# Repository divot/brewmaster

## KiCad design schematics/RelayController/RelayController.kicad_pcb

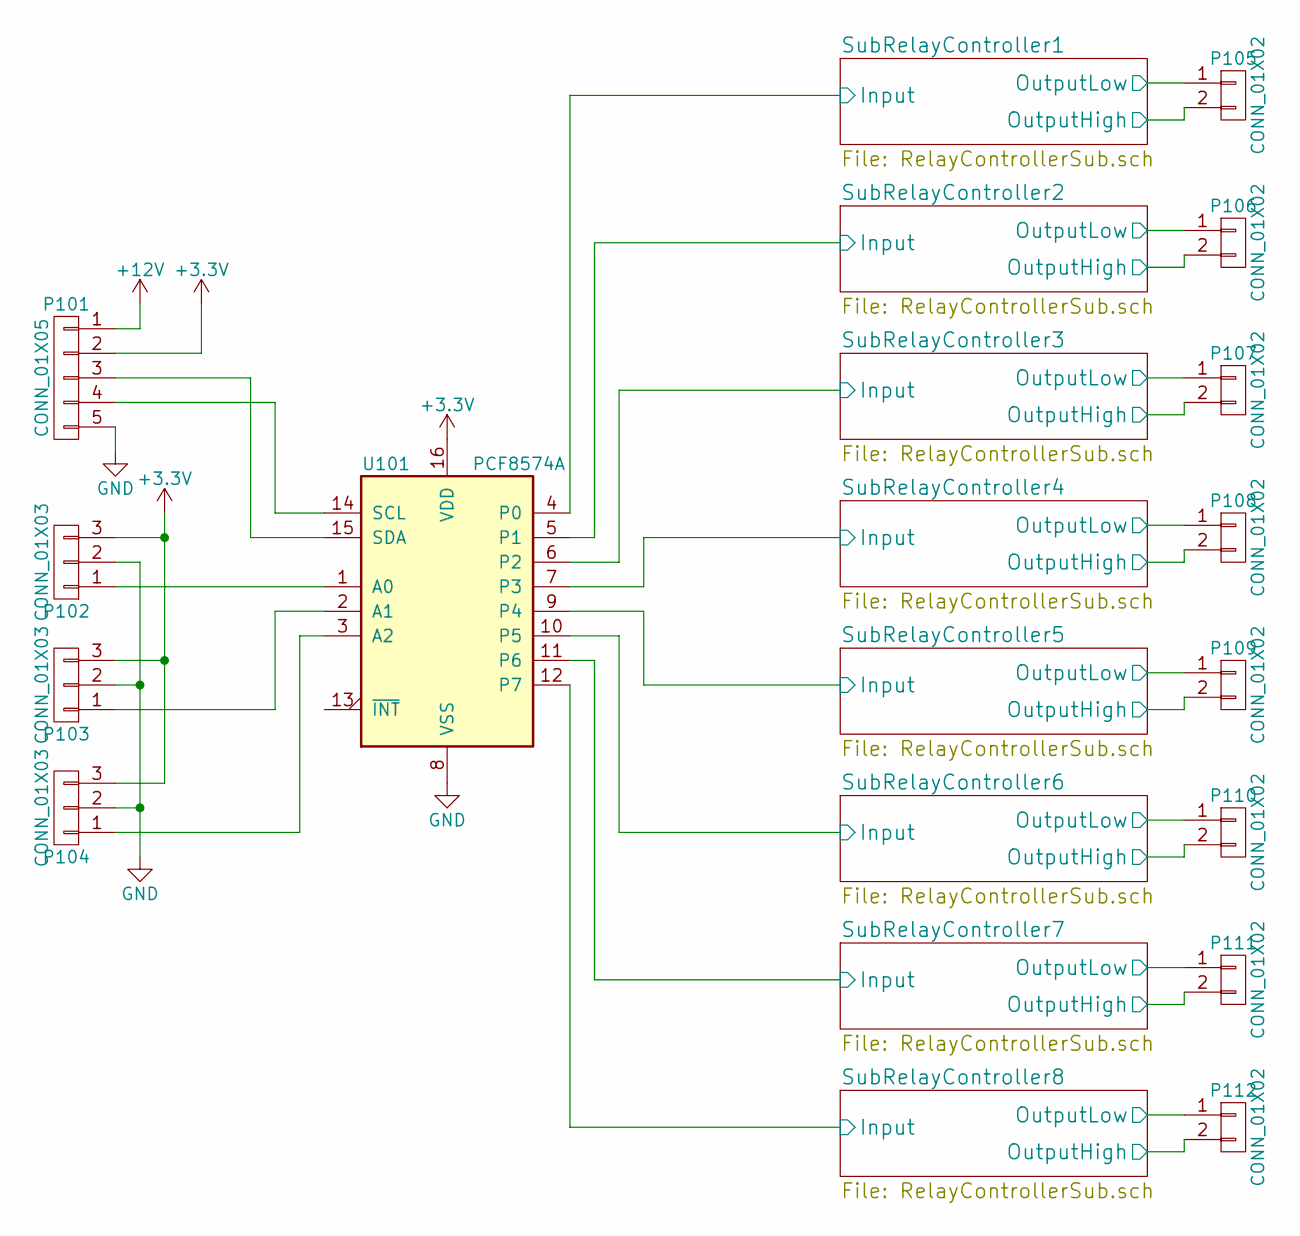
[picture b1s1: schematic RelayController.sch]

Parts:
P101: CONN_01X05; Pin_Header_Angled_1x05
P102, P103, P104: CONN_01X03; Pin_Header_Straight_1x03
P105, P106, P107, P108, P109, P110, P111, P112: CONN_01X02; Pin_Header_Angled_1x02
U101: PCF8574A; DIP-16_W7.62mm_LongPads

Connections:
+3V3: P101.2, P102.3, P103.3, P104.3, U101.16 (VDD); also elsewhere on the board
+12V: P101.1, P105.2, P106.2, P107.2, P108.2, P109.2, P110.2, P111.2, P112.2; also elsewhere on the board
/SubRelayController1/Input: U101.4 (P0); also elsewhere on the board
/SubRelayController1/OutputLow: P105.1; also elsewhere on the board
/SubRelayController2/Input: U101.5 (P1); also elsewhere on the board
/SubRelayController2/OutputLow: P106.1; also elsewhere on the board
/SubRelayController3/Input: U101.6 (P2); also elsewhere on the board
/SubRelayController3/OutputLow: P107.1; also elsewhere on the board
/SubRelayController4/Input: U101.7 (P3); also elsewhere on the board
/SubRelayController4/OutputLow: P108.1; also elsewhere on the board
/SubRelayController5/Input: U101.9 (P4); also elsewhere on the board
/SubRelayController5/OutputLow: P109.1; also elsewhere on the board
/SubRelayController6/Input: U101.10 (P5); also elsewhere on the board
/SubRelayController6/OutputLow: P110.1; also elsewhere on the board
/SubRelayController7/Input: U101.11 (P6); also elsewhere on the board
/SubRelayController7/OutputLow: P111.1; also elsewhere on the board
/SubRelayController8/Input: U101.12 (P7); also elsewhere on the board
/SubRelayController8/OutputLow: P112.1; also elsewhere on the board
GND: P101.5, P102.2, P103.2, P104.2, U101.8 (VSS); also elsewhere on the board
unnamed: P101.3, U101.15 (SDA)
unnamed: P101.4, U101.14 (SCL)
unnamed: P102.1, U101.1 (A0)
unnamed: P103.1, U101.2 (A1)
unnamed: P104.1, U101.3 (A2)

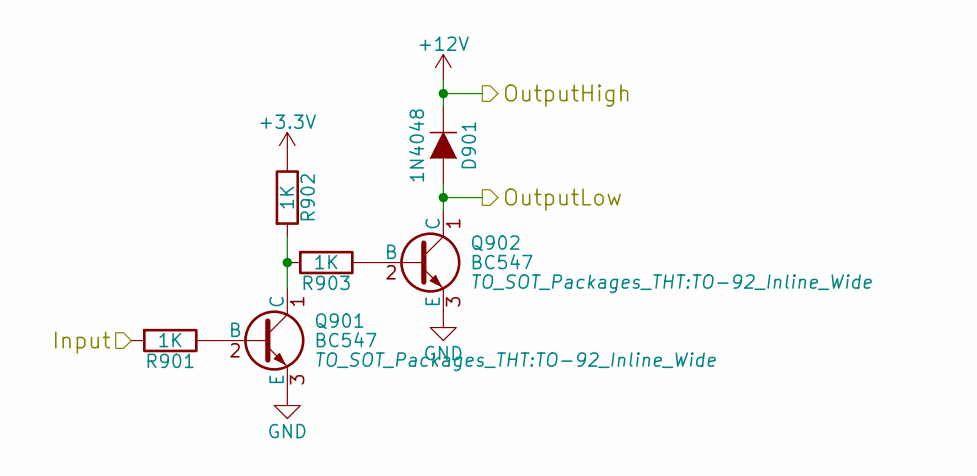
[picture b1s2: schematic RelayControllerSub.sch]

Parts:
D201: 1N4048; Diode_DO-35_SOD27_Horizontal_RM10
Q201, Q202: BC547; TO-92_Inline_Wide
R201, R202, R203: 1K; Resistor_Horizontal_RM10mm

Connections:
+3V3: R202.1; also elsewhere on the board
+12V: D201.1 (K); also elsewhere on the board
/SubRelayController1/Input: R201.2; also elsewhere on the board
/SubRelayController1/OutputLow: D201.2 (A), Q202.1 (C); also elsewhere on the board
GND: Q201.3 (E), Q202.3 (E); also elsewhere on the board
unnamed: Q201.1 (C), R202.2, R203.2
unnamed: Q201.2 (B), R201.1
unnamed: Q202.2 (B), R203.1

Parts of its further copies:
D301, D401, D501, D601, D701, D801, D901: 1N4048; Diode_DO-35_SOD27_Horizontal_RM10
Q301, Q302, Q401, Q402, Q501, Q502, Q601, Q602, Q701, Q702, Q801, Q802, Q901, Q902: BC547; TO-92_Inline_Wide
R301, R302, R303, R401, R402, R403, R501, R502, R503, R601, R602, R603, R701, R702, R703, R801, R802, R803, R901, R902, R903: 1K; Resistor_Horizontal_RM10mm

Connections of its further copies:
+3V3: R302.1, R402.1, R502.1, R602.1, R702.1, R802.1, R902.1; also elsewhere on the board
+12V: D301.1 (K), D401.1 (K), D501.1 (K), D601.1 (K), D701.1 (K), D801.1 (K), D901.1 (K); also elsewhere on the board
/SubRelayController2/Input: R301.2; also elsewhere on the board
/SubRelayController2/OutputLow: D301.2 (A), Q302.1 (C); also elsewhere on the board
/SubRelayController3/Input: R401.2; also elsewhere on the board
/SubRelayController3/OutputLow: D401.2 (A), Q402.1 (C); also elsewhere on the board
/SubRelayController4/Input: R501.2; also elsewhere on the board
/SubRelayController4/OutputLow: D501.2 (A), Q502.1 (C); also elsewhere on the board
/SubRelayController5/Input: R601.2; also elsewhere on the board
/SubRelayController5/OutputLow: D601.2 (A), Q602.1 (C); also elsewhere on the board
/SubRelayController6/Input: R701.2; also elsewhere on the board
/SubRelayController6/OutputLow: D701.2 (A), Q702.1 (C); also elsewhere on the board
/SubRelayController7/Input: R801.2; also elsewhere on the board
/SubRelayController7/OutputLow: D801.2 (A), Q802.1 (C); also elsewhere on the board
/SubRelayController8/Input: R901.2; also elsewhere on the board
/SubRelayController8/OutputLow: D901.2 (A), Q902.1 (C); also elsewhere on the board
GND: Q301.3 (E), Q302.3 (E), Q401.3 (E), Q402.3 (E), Q501.3 (E), Q502.3 (E), Q601.3 (E), Q602.3 (E), Q701.3 (E), Q702.3 (E), Q801.3 (E), Q802.3 (E), Q901.3 (E), Q902.3 (E); also elsewhere on the board
unnamed: Q301.1 (C), R302.2, R303.2
unnamed: Q301.2 (B), R301.1
unnamed: Q302.2 (B), R303.1
unnamed: Q401.1 (C), R402.2, R403.2
unnamed: Q401.2 (B), R401.1
unnamed: Q402.2 (B), R403.1
unnamed: Q501.1 (C), R502.2, R503.2
unnamed: Q501.2 (B), R501.1
unnamed: Q502.2 (B), R503.1
unnamed: Q601.1 (C), R602.2, R603.2
unnamed: Q601.2 (B), R601.1
unnamed: Q602.2 (B), R603.1
unnamed: Q701.1 (C), R702.2, R703.2
unnamed: Q701.2 (B), R701.1
unnamed: Q702.2 (B), R703.1
unnamed: Q801.1 (C), R802.2, R803.2
unnamed: Q801.2 (B), R801.1
unnamed: Q802.2 (B), R803.1
unnamed: Q901.1 (C), R902.2, R903.2
unnamed: Q901.2 (B), R901.1
unnamed: Q902.2 (B), R903.1

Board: 2 copper layers, 61 parts (0 on the bottom side), 48 nets, no tracks yet.

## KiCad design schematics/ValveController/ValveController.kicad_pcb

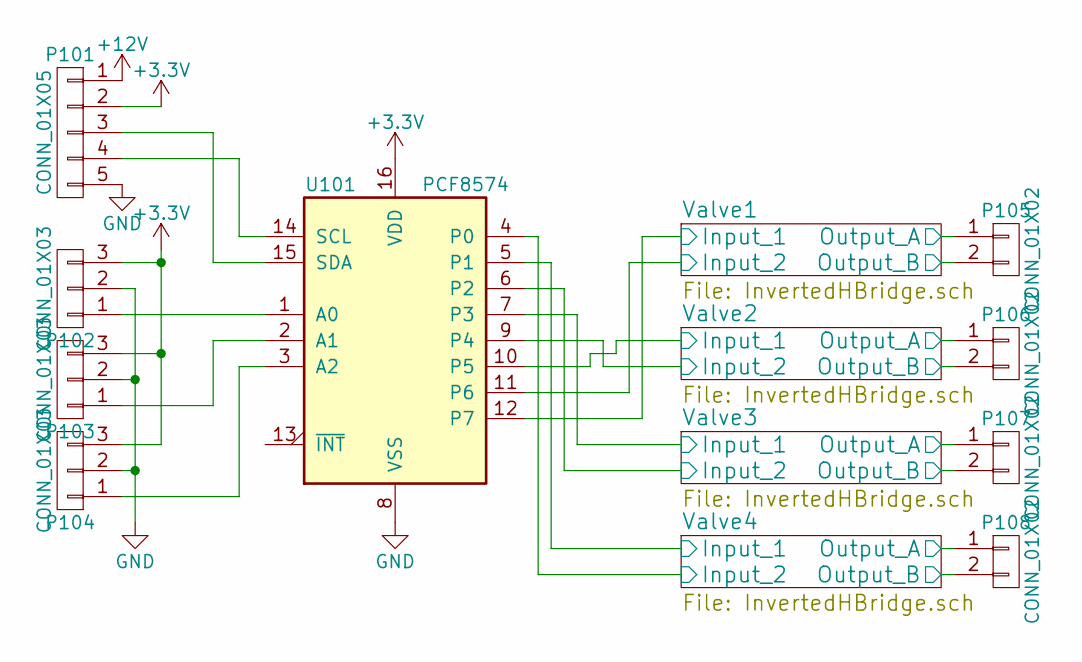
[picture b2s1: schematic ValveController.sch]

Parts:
P101: CONN_01X05; Pin_Header_Angled_1x05
P102, P103, P104: CONN_01X03; Pin_Header_Straight_1x03
P105, P106, P107, P108: CONN_01X02; Pin_Header_Angled_1x02
U101: PCF8574; DIP-16_W7.62mm_LongPads

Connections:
+3V3: P101.2, P102.3, P103.3, P104.3, U101.16 (VDD); also elsewhere on the board
+12V: P101.1; also elsewhere on the board
/Valve1/Input_1: U101.12 (P7); also elsewhere on the board
/Valve1/Input_2: U101.11 (P6); also elsewhere on the board
/Valve1/Output_A: P105.1; also elsewhere on the board
/Valve1/Output_B: P105.2; also elsewhere on the board
/Valve2/Input_1: U101.10 (P5); also elsewhere on the board
/Valve2/Input_2: U101.9 (P4); also elsewhere on the board
/Valve2/Output_A: P106.1; also elsewhere on the board
/Valve2/Output_B: P106.2; also elsewhere on the board
/Valve3/Input_1: U101.7 (P3); also elsewhere on the board
/Valve3/Input_2: U101.6 (P2); also elsewhere on the board
/Valve3/Output_A: P107.1; also elsewhere on the board
/Valve3/Output_B: P107.2; also elsewhere on the board
/Valve4/Input_1: U101.5 (P1); also elsewhere on the board
/Valve4/Input_2: U101.4 (P0); also elsewhere on the board
/Valve4/Output_A: P108.1; also elsewhere on the board
/Valve4/Output_B: P108.2; also elsewhere on the board
GND: P101.5, P102.2, P103.2, P104.2, U101.8 (VSS); also elsewhere on the board
unnamed: P101.3, U101.15 (SDA)
unnamed: P101.4, U101.14 (SCL)
unnamed: P102.1, U101.1 (A0)
unnamed: P103.1, U101.2 (A1)
unnamed: P104.1, U101.3 (A2)

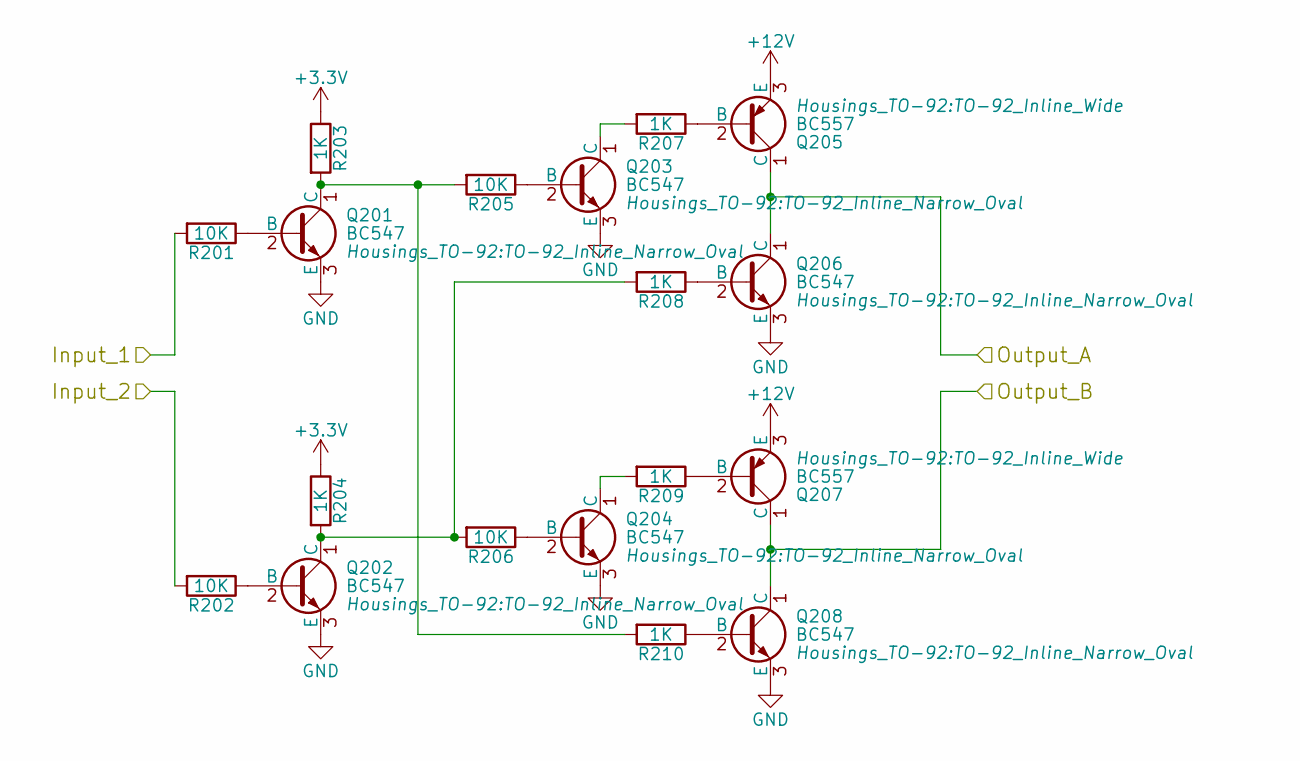
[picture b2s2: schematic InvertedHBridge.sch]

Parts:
Q201, Q202, Q203, Q204, Q206, Q208: BC547; TO-92_Inline_Narrow_Oval
Q205, Q207: BC557; TO-92_Inline_Wide
R201, R202, R205, R206: 10K; Resistor_Horizontal_RM10mm
R203, R204, R207, R208, R209, R210: 1K; Resistor_Horizontal_RM10mm

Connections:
+3V3: R203.1, R204.1; also elsewhere on the board
+12V: Q205.3 (E), Q207.3 (E); also elsewhere on the board
/Valve1/Input_1: R201.2; also elsewhere on the board
/Valve1/Input_2: R202.2; also elsewhere on the board
/Valve1/Output_A: Q205.1 (C), Q206.1 (C); also elsewhere on the board
/Valve1/Output_B: Q207.1 (C), Q208.1 (C); also elsewhere on the board
GND: Q201.3 (E), Q202.3 (E), Q203.3 (E), Q204.3 (E), Q206.3 (E), Q208.3 (E); also elsewhere on the board
unnamed: Q201.1 (C), R203.2, R205.2, R210.2
unnamed: Q201.2 (B), R201.1
unnamed: Q202.1 (C), R204.2, R206.2, R208.2
unnamed: Q202.2 (B), R202.1
unnamed: Q203.1 (C), R207.2
unnamed: Q203.2 (B), R205.1
unnamed: Q204.1 (C), R209.2
unnamed: Q204.2 (B), R206.1
unnamed: Q205.2 (B), R207.1
unnamed: Q206.2 (B), R208.1
unnamed: Q207.2 (B), R209.1
unnamed: Q208.2 (B), R210.1

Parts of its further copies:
Q301, Q302, Q303, Q304, Q306, Q308, Q401, Q402, Q403, Q404, Q406, Q408, Q501, Q502, Q503, Q504, Q506, Q508: BC547; TO-92_Inline_Narrow_Oval
Q305, Q307, Q405, Q407, Q505, Q507: BC557; TO-92_Inline_Wide
R301, R302, R305, R306, R401, R402, R405, R406, R501, R502, R505, R506: 10K; Resistor_Horizontal_RM10mm
R303, R304, R307, R308, R309, R310, R403, R404, R407, R408, R409, R410, R503, R504, R507, R508, R509, R510: 1K; Resistor_Horizontal_RM10mm

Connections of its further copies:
+3V3: R303.1, R304.1, R403.1, R404.1, R503.1, R504.1; also elsewhere on the board
+12V: Q305.3 (E), Q307.3 (E), Q405.3 (E), Q407.3 (E), Q505.3 (E), Q507.3 (E); also elsewhere on the board
/Valve2/Input_1: R301.2; also elsewhere on the board
/Valve2/Input_2: R302.2; also elsewhere on the board
/Valve2/Output_A: Q305.1 (C), Q306.1 (C); also elsewhere on the board
/Valve2/Output_B: Q307.1 (C), Q308.1 (C); also elsewhere on the board
/Valve3/Input_1: R401.2; also elsewhere on the board
/Valve3/Input_2: R402.2; also elsewhere on the board
/Valve3/Output_A: Q405.1 (C), Q406.1 (C); also elsewhere on the board
/Valve3/Output_B: Q407.1 (C), Q408.1 (C); also elsewhere on the board
/Valve4/Input_1: R501.2; also elsewhere on the board
/Valve4/Input_2: R502.2; also elsewhere on the board
/Valve4/Output_A: Q505.1 (C), Q506.1 (C); also elsewhere on the board
/Valve4/Output_B: Q507.1 (C), Q508.1 (C); also elsewhere on the board
GND: Q301.3 (E), Q302.3 (E), Q303.3 (E), Q304.3 (E), Q306.3 (E), Q308.3 (E), Q401.3 (E), Q402.3 (E), Q403.3 (E), Q404.3 (E), Q406.3 (E), Q408.3 (E), Q501.3 (E), Q502.3 (E), Q503.3 (E), Q504.3 (E), Q506.3 (E), Q508.3 (E); also elsewhere on the board
unnamed: Q301.1 (C), R303.2, R305.2, R310.2
unnamed: Q301.2 (B), R301.1
unnamed: Q302.1 (C), R304.2, R306.2, R308.2
unnamed: Q302.2 (B), R302.1
unnamed: Q303.1 (C), R307.2
unnamed: Q303.2 (B), R305.1
unnamed: Q304.1 (C), R309.2
unnamed: Q304.2 (B), R306.1
unnamed: Q305.2 (B), R307.1
unnamed: Q306.2 (B), R308.1
unnamed: Q307.2 (B), R309.1
unnamed: Q308.2 (B), R310.1
unnamed: Q401.1 (C), R403.2, R405.2, R410.2
unnamed: Q401.2 (B), R401.1
unnamed: Q402.1 (C), R404.2, R406.2, R408.2
unnamed: Q402.2 (B), R402.1
unnamed: Q403.1 (C), R407.2
unnamed: Q403.2 (B), R405.1
unnamed: Q404.1 (C), R409.2
unnamed: Q404.2 (B), R406.1
unnamed: Q405.2 (B), R407.1
unnamed: Q406.2 (B), R408.1
unnamed: Q407.2 (B), R409.1
unnamed: Q408.2 (B), R410.1
unnamed: Q501.1 (C), R503.2, R505.2, R510.2
unnamed: Q501.2 (B), R501.1
unnamed: Q502.1 (C), R504.2, R506.2, R508.2
unnamed: Q502.2 (B), R502.1
unnamed: Q503.1 (C), R507.2
unnamed: Q503.2 (B), R505.1
unnamed: Q504.1 (C), R509.2
unnamed: Q504.2 (B), R506.1
unnamed: Q505.2 (B), R507.1
unnamed: Q506.2 (B), R508.1
unnamed: Q507.2 (B), R509.1
unnamed: Q508.2 (B), R510.1

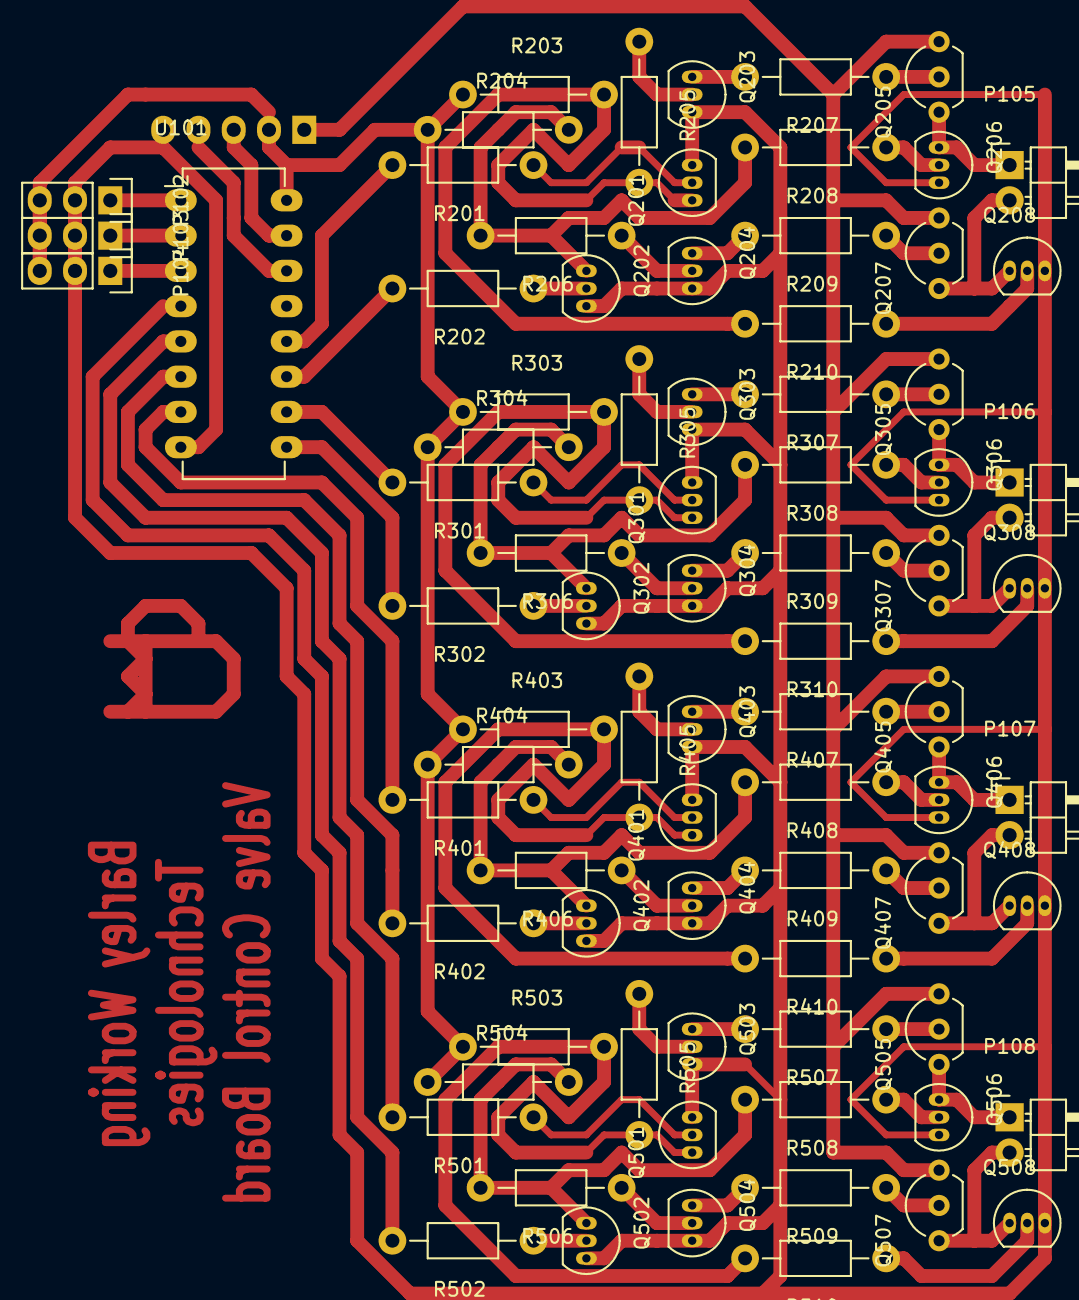
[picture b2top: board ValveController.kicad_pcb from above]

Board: 2 copper layers, 81 parts (1 on the bottom side), 72 nets.

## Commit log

2015-04-29 First commit. I think component is fine. Kettle and switch need to be updated to be components
2015-05-02 Slight tweaks to component get_all and attach/detach
2015-05-02 Converted switch to be a component container, and added timed on/off
2015-05-02 Added base Valve class and my three-wire valve
2015-05-02 Added solenoid valve
2015-10-23 Added in a load of old code that I hacked together. I need a serious design and rethink of everything
2015-10-23 I should really setup a gitignore
2015-10-24 Created a liquid modelling design based around finding routes from the get go. Complete with tests.
2015-10-25 Moved the find_all_paths for each port into the Port class where it belongs, and cleaned up the unnecessary passing around of variables.
2015-10-25 Finally started a gitignore
2015-10-25 Started moving code around. Hiding old stuff I don't want to get rid of yet, and starting to set up a proper src layout|
2015-10-25 Splitting LiquidComponent into its base components.
2015-10-25 Fiddling with test paths. I hate to do this but PYTHONPATH is being a bitch
2015-10-25 Introducing state to liquidcomponent
2015-10-25 Added in a real life two way valve and some test code. I really need to figure out a better test setup but I can't be arsed.
2015-11-01 Added in vague support for an expandable passable GPIO and PCF8574 GPIO expander
2015-11-01 Added in standard gpio too
2015-11-02 Tweaked GPIOs further to allow them to be specified as inverted. Also cleaned up bit writing for the expander version.
2015-11-02 Did some useless renaming
2015-11-02 Converted MISOL Two Way Valve to use the new GPIO objects.
2015-11-02 Tweaked MISOL valve to keep track of state a bit better, and to allow you to wait on a state change.
2015-11-02 Changed it so that the valve outputs are switched off when they're finished.
2015-11-02 Added in slight testing code for my current setup. It works!!
2015-11-19 Added in ValveController schematics. First version that I made the pcb and it all went wrong (aka fried raspberry pi).I think the main reason for this was I wan't careful enough with my multimeter pr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
2015-11-29 Updated Valve Controller with bigger pads
2015-11-29 Added pump controller schematic
2015-11-29 Added Relay Controller Schematic
2021-07-27 Add without checking
